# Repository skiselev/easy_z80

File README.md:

# Easy Z80
An easy to build Zilog Z80 based single board computer

## Table of Contents
* [Introduction](#introduction)
* [Specifications](#specifications)
* [Hardware Documentation](#hardware-documentation)
  * [Schematic and PCB Layout](#schematic-and-pcb-layout)
  * [Connectors and Jumpers](#connectors-and-jumpers)
  * [Bill of Materials](#bill-of-materials)
* [Firmware Documentation](#firmware-documentation)
  * [BIOS and OS](#bios-and-os)
  * [SPLD Fuse Map](#spld-fuse-map)
* [Release Notes](#release-notes)
  * [Changes](#changes)
  * [Known Issues](#known-issues)
  * [Wishlist](#wishlist)

## Introduction
My son Max asked me what it takes to build a computer, and whether or not he can design and build one himself. This project is our attempt to design and build a simple, easy to understand, yet capable single board computer.
It reuses the same memory paging mechanism I've implemented in Zeta SBC V2. It uses the Zilog Z80 SIO/O, Z80 CTC peripheral ICs, and implements daisy chain mode 2 interrupt configuration.

## Specifications
* Processor: Zilog Z80 CPU (CMOS version - Z84C00)
* Memory: 512 KiB battery-backed SRAM, 512 KiB Flash ROM
* I/O:
  * Zilog Z80 CTC - Programmable timer used for periodic interrupts and (optionally) for generating UART clock
  * Zilog Z80 SIO - Dual channel serial interface, used for console and for connecting to other peripheral devices
* Bus: [RC2014](https://rc2014.co.uk/) compatible
* Microprocessor Supervisor:
  * Reset generation
  * SRAM battery backup
  * Power failure NMI
  * Watchdog (optional)

## Hardware Documentation

For the version 1.0 schematic, PCB layout, and bill of materials please refer to [tag v1.0](https://github.com/skiselev/easy_z80/tree/v1.0)

### Schematic and PCB Layout

[Schematic - Version 1.1](KiCad/Easy_Z80-Schematic-1.1.pdf)

[PCB Layout - Version 1.1](KiCad/Easy_Z80-Board-1.1.pdf)

### Connectors and Jumpers

#### J1 - Power
Connect regulated +5V power supply to this connector.

Pin                     | Signal Name | Description
----------------------- | ----------- | -----------
Tip (the inner contact)	| VCC         | Positive terminal - +5V
Barrel / sleeve	        | GND         | Negative terminal - ground

#### J2, J3 - Serial Channel A and Serial Channel B
Pin    | Signal Name | Description
------ | ----------- | -----------
1	     | DCD         |	Carrier Detect; Not used - Not connected on the SBC
2	     | RXA, RXB    |	Receive Data; Input to SBC
3	     | TXA, TXB    |	Transmit Data; Output from SBC
4	     | DTR         |	Data Terminal Ready; Not used - Not connected on the SBC
5	     | GND         |	Connected to the SBC GND signal
6	     | DSR         | Data Set Ready; Not used - Not connected on the SBC
7      |	RTSA, RTSB  | Request to Send; Output from SBC
8	     | CTSA, CTSB  | Clear to Send; Input to SBC
9	     | RI	         | Ring Indicator; Not used - Not connected on the SBC
Shield	| DE9 Shield	 | Connected to the SBC GND signal

#### J4 - NVRAM Battery
Connect 3V battery for SRAM backup to this connector.

**Important: If the SRAM battery backup is not desired, short J4 with a jumper. Do not leave this connector open.**

Pin | Signal Name | Description
--- | ----------- | -----------
1  	| VBAT        | Positive terminal - +3V
2   | GND         | Negative terminal - ground

#### J5, J6, J7 - RC2014 Bus
Pin   | Signal Name | Description         | Pin  | Signal Name | Description
----- | ----------- | ------------------- | ---- | ----------- | -----------
J5-1  | A15         | Address A15; Output |      |             |
J5-2  | A14         | Address A14; Output |      |             |
J5-3  | A13         | Address A13; Output |      |             |
J5-4  | A12         | Address A12; Output |      |             |
J5-5  | A11         | Address A11; Output |      |             |
J5-6  | A10         | Address A10; Output |      |             |
J5-7  | A9          | Address A9; Output  |      |             |
J5-8  | A8          | Address A8; Output  |      |             |
J5-9  | A7          | Address A7; Output  |      |             |
J5-10 | A6          | Address A6; Output  |      |             |
J5-11 | A5          | Address A5; Output  |      |             |
J5-12 | A4          | Address A4; Output  |      |             |
J5-13 | A3          | Address A3; Output  |      |             |
J5-14 | A2          | Address A2; Output  |      |             |
J5-15 | A1          | Address A1; Output  |      |             |
J5-16 | A0          | Address A0; Output  |      |             |
J5-17 | GND         | Ground              | J6-1 | GND         | Ground
J5-18 | VCC         | Power Supply - +5V  | J6-2 | VCC         | Power Supply - +5V
J5-19 | /M1         | Machine Cycle One; Output | J6-3| /RFSH | DRAM refresh; Output
J5-20 | /RESET      | Reset; Output       | J6-4 | N/C         | Not connected
J5-21 | CPU_CLK     | CPU Clock; Output   | J6-5 | UART_CLK    | UART Clock (1.8432 MHz); Output
J5-22 | /INT        | Interrupt; Input    | J6-6 | /BUSACK     | DMA Bus Acknowledge; Output
J5-23 | /MREQ       | Memory Request; Output | J6-7 | /HALT    | Halt; Output
J5-24 | /WR         | Write Request; Output | J6-8 | /BUSREQ   | DMA Bus Request; Input
J5-25 | /RD         | Read Request; Output | J6-9 | /WAIT      | Wait; Input
J5-26 | /IORQ       | Input/Output Request; Output | J6-10 | /NMI | Non-maskable Interrupt; Input
J5-27 | D0          | Data D0; Input/Output |    |             |
J5-28 | D1          | Data D1; Input/Output |    |             |
J5-29 | D2          | Data D2; Input/Output |    |             |
J5-30 | D3          | Data D3; Input/Output |    |             |
J5-31 | D4          | Data D4; Input/Output |    |             |
J5-32 | D5          | Data D5; Input/Output |    |             |
J5-33 | D6          | Data D6; Input/Output |    |             |
J5-34 | D7          | Data D7; Input/Output |    |             |
J5-35 | TXDA        | Channel A, Transmit Data; Output | J7-1 | TXDB | Channel B, Transmit Data; Output
J5-36 | RXDA        | Channel A, Receive Data; Input   | J7-2 | RXDB | Channel B, Receive Data; Input
J5-37 | USR1        | User Pin 1, Not connected | J7-3 | USR5  | User Pin 5, Not connected 
J5-38 | IEI         | Interrupt Enable Input  | J7-4 | USR6    | User Pin 6, Not connected 
J5-39 | IEO         | Interrupt Enable Output | J7-5 | USR7    | User Pin 7, Not connected 

#### JP1 - Serial Channel A Clock Select
Position        | Description
--------------- | -----------
*1-2 (default)* | 1.8432 MHz (115200 bps if using x16 mode)
2-3             | Programmable using CTC channel 0

#### JP2 - Serial Channel B Clock Select
Position        | Description
--------------- | -----------
*1-2 (default)* | 1.8432 MHz (115200 bps if using x16 mode)
2-3             | Programmable using CTC channel 1

### Bill of Materials

#### Version 1.1

[Easy Z80 project on Mouser.com](https://www.mouser.com/ProjectManager/ProjectDetail.aspx?AccessID=f16751cb33) - View and order all components except of the PCB.

[Easy Z80 project on OSH Park](https://oshpark.com/shared_projects/Rt7SBcRg) - View and order the PCB.

Component type     | Reference | Description                                 | Quantity | Possible sources and notes 
------------------ | --------- | ------------------------------------------- | -------- | --------------------------
PCB                |           | Easy Z80 PCB - Version 1.1                  | 1        | Refer to the [RetroBrew Computers Board Inventory](https://www.retrobrewcomputers.org/doku.php?id=boardinventory#minimal_8085_z80_single_board_computer) page for ordering information, or order from a PCB manufacturer of your choice using provided Gerber or KiCad files
Integrated Circuit | U1        | Z80 CPU, CMOS, 40 pin DIP - Z84C00xxPEG     | 1        | Mouser [692-Z84C0010PEG](https://www.mouser.com/ProductDetail/692-Z84C0010PEG)
Integrated Circuit | U2        | Z80 CTC, CMOS, 28 pin DIP - Z84C30xxPEG     | 1        | Mouser [692-Z84C3010PEG](https://www.mouser.com/ProductDetail/692-Z84C3010PEG)
Integrated Circuit | U3        | Z80 SIO/0, CMOS, 40 pin DIP - Z84C40xxPEG   | 1        | Mouser [692-Z84C4010PEG](https://www.mouser.com/ProductDetail/692-Z84C4010PEG)
Integrated Circuit | U4        | 512 KiB SRAM, 32 pin DIP - AS6C4008         | 1        | Mouser [913-AS6C4008-55PCN](https://www.mouser.com/ProductDetail/913-AS6C4008-55PCN)
Integrated Circuit | U5        | 512 KiB Flash ROM, 32 pin DIP - SST39SF040  | 1        | Mouser [804-39SF0407CPHE](https://www.mouser.com/ProductDetail/804-39SF0407CPHE)
Integrated Circuit | U6        | Microprocessor Supervisory Circuit - MAX693 | 1        | Mouser [584-ADM693ANZ](https://www.mouser.com/ProductDetail/584-ADM693ANZ); Possible alternatives: MAX693, LTC693, ADM691, MAX691, LTC691, ADM695, MAX695, LTC965, LTC1235
Integrated Circuit | U7, U8    | Dual RS-232 Driver/Receiver - MAX232A       | 2        | Mouser [595-TRS202EIN](https://www.mouser.com/ProductDetail/595-TRS202EIN/)
Integrated Circuit | U9        | Simple Programmable Logic Device - ATF16V8B | 1        | Mouser [556-AF16V8B15PU](https://www.mouser.com/ProductDetail/556-AF16V8B15PU)
Integrated Circuit | U10, U11  | 4-by-4 Register File - 74HC670              | 2        | Mouser [595-CD74HC670E](https://www.mouser.com/ProductDetail/595-CD74HC670E)
Integrated Circuit | U12       | Dual Flip Flop - 74HC74                     | 1        | Mouser [595-SN74HC74N](https://www.mouser.com/ProductDetail/595-SN74HC74N)
Oscillator         | QG1       | 10 MHz, CMOS oscillator, Half Can           | 1        | Mouser [774-MXO45HS-3C-10.0](https://www.mouser.com/ProductDetail/774-MXO45HS-3C-10.0)
Oscillator         | QG2       | 1.8432 MHz, CMOS oscillator, Half Can       | 1        | Mouser [774-MXO45HS-3C-1.8](https://www.mouser.com/ProductDetail/774-MXO45HS-3C-1.8)
LED                | D1        | 3 mm, green LED indicator                   | 1        | Mouser [859-LTL-4231N](https://www.mouser.com/ProductDetail/859-LTL-4231N)
Tactile Button     | SW1       | 6 mm tactile button, right angle            | 1        | Mouser [653-B3F-3152](https://www.mouser.com/ProductDetail/653-B3F-3152)
Connector          | J1        | DC Power Jack, 2mm                          | 1        | Mouser [806-KLDX-0202-A](https://www.mouser.com/ProductDetail/806-KLDX-0202-A)
Connector          | J2, J3    | Sub-D DE9M, Right Angle, PCB mount          | 2        | Mouser [806-K22X-E9P-N-99](https://www.mouser.com/ProductDetail/806-K22X-E9P-N-99)
Connector          | J4        | 2 Pin Header with Friction Lock             | 1        | Mouser [571-6404562](https://www.mouser.com/ProductDetail/571-6404562)
Pin Header         | J5 - J7   | 40x2 Pin Header, 2.54 mm Pitch, Right Angle | 1        | Mouser [571-9-103326-0](https://www.mouser.com/ProductDetail/571-9-103326-0)
Capacitor          | C1 - C14, C16 - C23  | 0.1 uF, MLCC, 5 mm Pitch         | 22       | Mouser [594-K104K15X7RF53H5](https://www.mouser.com/ProductDetail/594-K104K15X7RF53H5)
Capacitor          | C24       | 47 uF, 25V, Aluminum Organic Polymer        | 1        | Mouser [80-A750EK476M1EAAE40](https://www.mouser.com/ProductDetail/80-A750EK476M1EAAE40)
Resistor Array     | RN1 - RN3 | 4.7 k, bussed, 5 pin SIP                    | 3        | Mouser [652-4605X-AP1-472LF](https://www.mouser.com/ProductDetail/652-4605X-AP1-472LF)
Resistor Array     | RN4       | 4.7 k, bussed, 9 pin SIP                    | 1        | Mouser [652-4609X-AP1-472LF](https://www.mouser.com/ProductDetail/652-4609X-AP1-472LF)
Resistor           | R1        | 470 ohm, axial                              | 1        | Mouser [603-MFR-25FRF52-470R](https://www.mouser.com/ProductDetail/603-MFR-25FRF52-470R) 
Resistor           | R2 - R4   | 10 kohm, 1% tolerance, axial                | 3        | Mouser [603-MFR-25FRF5210K](https://www.mouser.com/ProductDetail/603-MFR-25FRF5210K)
Resistor           | R5        | 29.4 kohm, 1% tolerance, axial              | 1        | Mouser [603-MFR-25FBF52-29K4](https://www.mouser.com/ProductDetail/603-MFR-25FBF52-29K4)
Trimmer Resistor   | RV1       | 2 kohm, through hole                        | 1        | Mouser [652-3362P-1-202LF](https://www.mouser.com/ProductDetail/652-3362P-1-202LF)
IC Socket          | U1, U3    | 40 pin DIP                                  | 2        | Mouser [517-4840-6000-CP](https://www.mouser.com/ProductDetail/517-4840-6000-CP)
IC Socket          | U4, U5    | 32 pin DIP                                  | 2        | Mouser [517-4832-6000-CP](https://www.mouser.com/ProductDetail/517-4832-6000-CP)
IC Socket          | U2        | 28 pin DIP                                  | 1        | Mouser [517-4828-6000-CP](https://www.mouser.com/ProductDetail/517-4828-6000-CP)
IC Socket          | U9        | 20 pin DIP                                  | 1        | Mouser [517-4820-3000-CP](https://www.mouser.com/ProductDetail/517-4820-3000-CP)
IC Socket          | U6 - U8, U10, U11 | 16 pin DIP                          | 5        | Mouser [517-4816-3000-CP](https://www.mouser.com/ProductDetail/517-4816-3000-CP)
IC Socket          | U12       | 14 pin DIP                                  | 1        | Mouser [517-4814-3000-CP](https://www.mouser.com/ProductDetail/517-4814-3000-CP)
Oscillator Socket  | QG1, QG2  | 4 pin DIP, Half Can                         | 2        | Mouser [535-1108800](https://www.mouser.com/ProductDetail/535-1108800)

## Firmware Documentation

### BIOS and OS

Easy Z80 is supported by [RomWBW](https://github.com/wwarthen/RomWBW) [v2.9.1](https://github.com/wwarthen/RomWBW/releases/tag/v2.9.1) and later. RomWBW includes BIOS, CP/M-80 2.2, Z-System, and a collection of utilities. It also should be possible to run [FUZIX](https://github.com/EtchedPixels/FUZIX) on this board.

### SPLD Fuse Map

Easy Z80 uses an ATF16V8/GAL16V8 SPLD (U9) for address decode logic. The [SPLD fuse map](SPLD/easy_z80_no_wdog.jed) and the [SPLD source code](SPLD/easy_z80_no_wdog.pld) are provided in [SPLD](SPLD) directory of this repository.

## Release Notes

### Changes
* Version 1.1
  * Add pull-up resistors on the data bus (RN4 - 4.7k) to support Z80 interrupt mode 0
  * Use 74HC series instead of 74HCT
  * Remove C15
  * Use RN reference for resistor arrays instead of RR
  * Update silkscreen:
    * Make RN1 reference and value visible
    * Update silkscreen of headers footprints, so that JP1 and JP2 don't cover the traces
    * Add project URL to the bottom silkscreen
* Version 1.0
  * Initial version

### Known Issues
* Version 1.0
  * Top silkscreen: RR1 reference and value are not visible. It should read "RR1, 4.7k"
  * Bottom silkscreen on JP1 and JP2 covers the trace connections, so they are not easily visible
  * Bottom silkscreen: No project URL. Should be [github.com/skiselev/easy_z80](https://github.com/skiselev/easy_z80)
  * Board will not reset when C15 is populated. Workaround: Do not populate this capacitor
  * Schematic and top silkscreen: Use 74HC series instead of 74HCT
  
### Wishlist
* Version 1.0
  * Add pull-ups on the data bus to support extension boards that were not designed for Z80 interrupt mode 2

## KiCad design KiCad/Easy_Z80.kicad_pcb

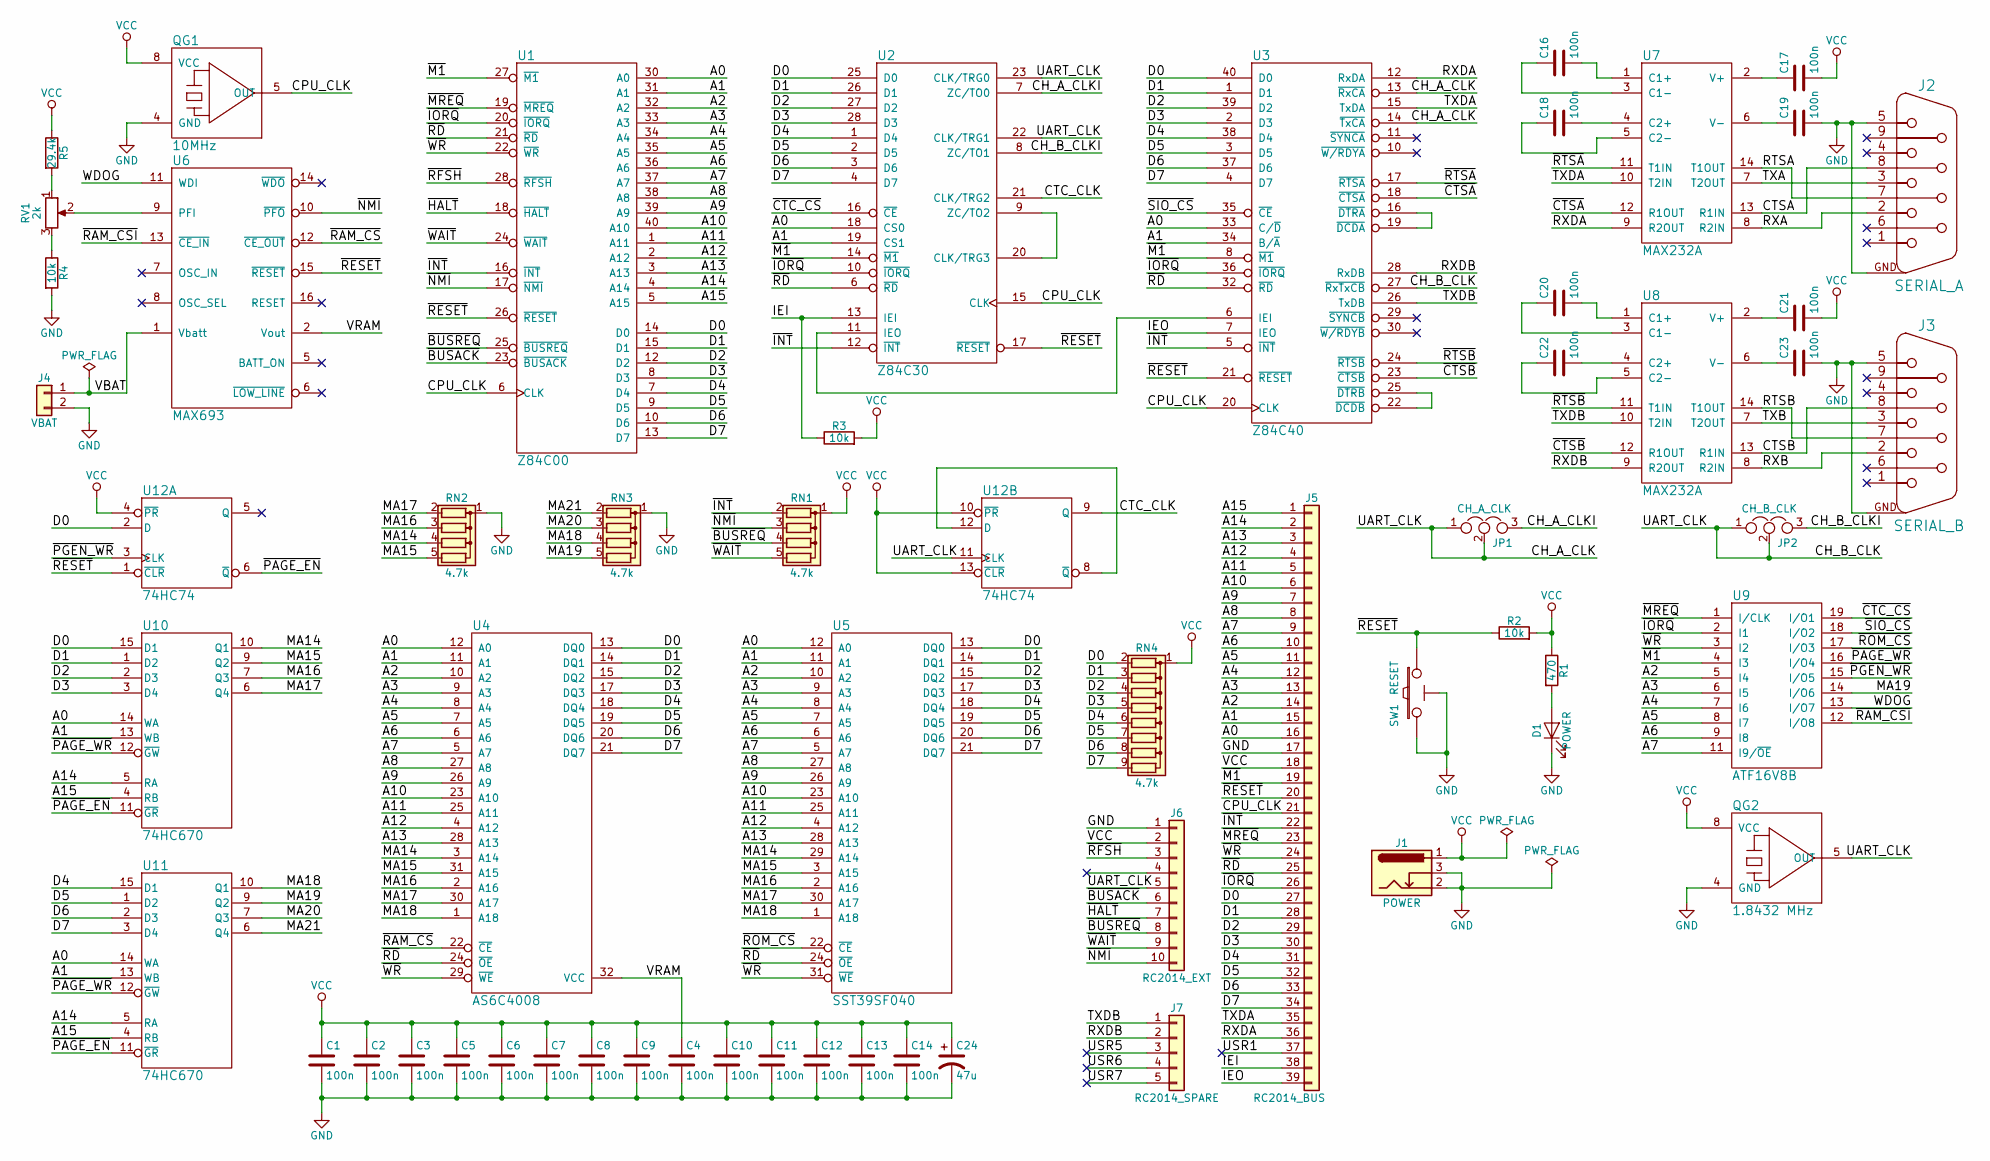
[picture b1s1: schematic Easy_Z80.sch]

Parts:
C1, C2, C3, C4, C5, C6, C7, C8, C9, C10, C11, C12, C13, C14, C16, C17, C18, C19, C20, C21, C22, C23: 100n; Cap_Cer_508
C24: 47u; Cap_Elec_Radial_6.3mm
D1: POWER; LED_3mm
J1: POWER; Conn_Power_Jack_Circular_Pads
J2: SERIAL_A; Conn_Dsub_DE9M
J3: SERIAL_B; Conn_Dsub_DE9M
J4: VBAT; Conn_Friction_Lock_2P_2.54mm
J5: RC2014_BUS; Conn_Pin_Header_39x1_2.54mm
J6: RC2014_EXT; Conn_Pin_Header_10x1_2.54mm
J7: RC2014_SPARE; Conn_Pin_Header_5x1_2.54mm
JP1: CH_A_CLK; Conn_Pin_Header_3x1_2.54mm
JP2: CH_B_CLK; Conn_Pin_Header_3x1_2.54mm
QG1: 10MHz; OSC_Half_Can_DIP8
QG2: 1.8432 MHz; OSC_Half_Can_DIP8
R1: 470; Res_762
R2, R3, R4: 10k; Res_762
R5: 29.4k; Res_762
RN1, RN2, RN3: 4.7k; Conn_SIL5
RN4: 4.7k; Conn_SIL9
RV1: 2k; Trimmer_Bourns_3362P
SW1: RESET; Switch_Tactile_6mm_Right
U1: Z84C00; IC_DIP40_600
U2: Z84C30; IC_DIP28_600
U3: Z84C40; IC_DIP40_600
U4: AS6C4008; IC_DIP32_600
U5: SST39SF040; IC_DIP32_600
U6: MAX693; IC_DIP16_300
U7, U8: MAX232A; IC_DIP16_300
U9: ATF16V8B; IC_DIP20_300
U10, U11: 74HC670; IC_DIP16_300
U12: 74HC74; IC_DIP14_300

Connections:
/A0: J5.16, U1.30 (A0), U2.18 (CS0), U3.33 (C/~D), U4.12 (A0), U5.12 (A0), U10.14 (WA), U11.14 (WA)
/A1: J5.15, U1.31 (A1), U2.19 (CS1), U3.34 (B/~A), U4.11 (A1), U5.11 (A1), U10.13 (WB), U11.13 (WB)
/A2: J5.14, U1.32 (A2), U4.10 (A2), U5.10 (A2), U9.5 (I4)
/A3: J5.13, U1.33 (A3), U4.9 (A3), U5.9 (A3), U9.6 (I5)
/A4: J5.12, U1.34 (A4), U4.8 (A4), U5.8 (A4), U9.7 (I6)
/A5: J5.11, U1.35 (A5), U4.7 (A5), U5.7 (A5), U9.8 (I7)
/A6: J5.10, U1.36 (A6), U4.6 (A6), U5.6 (A6), U9.9 (I8)
/A7: J5.9, U1.37 (A7), U4.5 (A7), U5.5 (A7), U9.11 (I9/~OE)
/A8: J5.8, U1.38 (A8), U4.27 (A8), U5.27 (A8)
/A9: J5.7, U1.39 (A9), U4.26 (A9), U5.26 (A9)
/A10: J5.6, U1.40 (A10), U4.23 (A10), U5.23 (A10)
/A11: J5.5, U1.1 (A11), U4.25 (A11), U5.25 (A11)
/A12: J5.4, U1.2 (A12), U4.4 (A12), U5.4 (A12)
/A13: J5.3, U1.3 (A13), U4.28 (A13), U5.28 (A13)
/A14: J5.2, U1.4 (A14), U10.5 (RA), U11.5 (RA)
/A15: J5.1, U1.5 (A15), U10.4 (RB), U11.4 (RB)
/CH_A_CLK: J6.5, JP1.1, JP1.2, JP2.1, JP2.2, QG2.5 (OUT), U2.22 (CLK/TRG1), U2.23 (CLK/TRG0), U3.13 (~RxCA), U3.14 (~TxCA), U3.27 (~RxTxCB), U12.11 (CLK)
/CH_A_CLKI: JP1.3, U2.7 (ZC/TO0)
/CH_B_CLKI: JP2.3, U2.8 (ZC/TO1)
/CPU_CLK: J5.21, QG1.5 (OUT), U1.6 (CLK), U2.15 (CLK), U3.20 (CLK)
/CTC_CLK: U2.21 (CLK/TRG2), U12.9 (Q)
/CTSA: J2.8, U7.13 (R1IN)
/CTSB: J3.8, U8.13 (R1IN)
/D0: J5.27, RN4.2 (R1), U1.14 (D0), U2.25 (D0), U3.40 (D0), U4.13 (DQ0), U5.13 (DQ0), U10.15 (D1), U12.2 (D)
/D1: J5.28, RN4.3 (R2), U1.15 (D1), U2.26 (D1), U3.1 (D1), U4.14 (DQ1), U5.14 (DQ1), U10.1 (D2)
/D2: J5.29, RN4.4 (R3), U1.12 (D2), U2.27 (D2), U3.39 (D2), U4.15 (DQ2), U5.15 (DQ2), U10.2 (D3)
/D3: J5.30, RN4.5 (R4), U1.8 (D3), U2.28 (D3), U3.2 (D3), U4.17 (DQ3), U5.17 (DQ3), U10.3 (D4)
/D4: J5.31, RN4.6 (R5), U1.7 (D4), U2.1 (D4), U3.38 (D4), U4.18 (DQ4), U5.18 (DQ4), U11.15 (D1)
/D5: J5.32, RN4.7 (R6), U1.9 (D5), U2.2 (D5), U3.3 (D5), U4.19 (DQ5), U5.19 (DQ5), U11.1 (D2)
/D6: J5.33, RN4.8 (R7), U1.10 (D6), U2.3 (D6), U3.37 (D6), U4.20 (DQ6), U5.20 (DQ6), U11.2 (D3)
/D7: J5.34, RN4.9 (R8), U1.13 (D7), U2.4 (D7), U3.4 (D7), U4.21 (DQ7), U5.21 (DQ7), U11.3 (D4)
/IEI: J5.38, R3.1, U2.13 (IEI)
/IEO: J5.39, U3.7 (IEO)
/MA14: RN2.4 (R3), U4.3 (A14), U5.29 (A14), U10.10 (Q1)
/MA15: RN2.5 (R4), U4.31 (A15), U5.3 (A15), U10.9 (Q2)
/MA16: RN2.3 (R2), U4.2 (A16), U5.2 (A16), U10.7 (Q3)
/MA17: RN2.2 (R1), U4.30 (A17), U5.30 (A17), U10.6 (Q4)
/MA18: RN3.4 (R3), U4.1 (A18), U5.1 (A18), U11.10 (Q1)
/MA19: RN3.5 (R4), U9.14 (I/O6), U11.9 (Q2)
/MA20: RN3.3 (R2), U11.7 (Q3)
/MA21: RN3.2 (R1), U11.6 (Q4)
/RTSA: J2.7, U7.14 (T1OUT)
/RTSB: J3.7, U8.14 (T1OUT)
/RXA: J2.2, U7.8 (R2IN)
/RXB: J3.2, U8.8 (R2IN)
/RXDA: J5.36, U3.12 (RxDA), U7.9 (R2OUT)
/RXDB: J7.2, U3.28 (RxDB), U8.9 (R2OUT)
/TXA: J2.3, U7.7 (T2OUT)
/TXB: J3.3, U8.7 (T2OUT)
/TXDA: J5.35, U3.15 (TxDA), U7.10 (T2IN)
/TXDB: J7.1, U3.26 (TxDB), U8.10 (T2IN)
/USR1: J5.37
/USR5: J7.3
/USR6: J7.4
/USR7: J7.5
/VBAT: J4.1, U6.1 (Vbatt)
/VRAM: C4.1, U4.32 (VCC), U6.2 (Vout)
/WDOG: U6.11 (WDI), U9.13 (I/O7)
/~BUSACK: J6.6, U1.23 (~BUSACK)
/~BUSREQ: J6.8, RN1.4 (R3), U1.25 (~BUSREQ)
/~CTC_CS: U2.16 (~CE), U9.19 (I/O1)
/~CTSA: U3.18 (~CTSA), U7.12 (R1OUT)
/~CTSB: U3.23 (~CTSB), U8.12 (R1OUT)
/~HALT: J6.7, U1.18 (~HALT)
/~INT: J5.22, RN1.2 (R1), U1.16 (~INT), U2.12 (~INT), U3.5 (~INT)
/~IORQ: J5.26, U1.20 (~IORQ), U2.10 (~IORQ), U3.36 (~IORQ), U9.2 (I1)
/~M1: J5.19, U1.27 (~M1), U2.14 (~M1), U3.8 (~M1), U9.4 (I3)
/~MREQ: J5.23, U1.19 (~MREQ), U9.1 (I/CLK)
/~NMI: J6.10, RN1.3 (R2), U1.17 (~NMI), U6.10 (~PFO)
/~PAGE_EN: U10.11 (~GR), U11.11 (~GR), U12.6 (~Q)
/~PAGE_WR: U9.16 (I/O4), U10.12 (~GW), U11.12 (~GW)
/~PGEN_WR: U9.15 (I/O5), U12.3 (CLK)
/~RAM_CS: U4.22 (~CE), U6.12 (~CE_OUT)
/~RAM_CSI: U6.13 (~CE_IN), U9.12 (I/O8)
/~RD: J5.25, U1.21 (~RD), U2.6 (~RD), U3.32 (~RD), U4.24 (~OE), U5.24 (~OE)
/~RESET: J5.20, R2.1, SW1.1, U1.26 (~RESET), U2.17 (~RESET), U3.21 (~RESET), U6.15 (~RESET), U12.1 (~CLR)
/~RFSH: J6.3, U1.28 (~RFSH)
/~ROM_CS: U5.22 (~CE), U9.17 (I/O3)
/~RTSA: U3.17 (~RTSA), U7.11 (T1IN)
/~RTSB: U3.24 (~RTSB), U8.11 (T1IN)
/~SIO_CS: U3.35 (~CE), U9.18 (I/O2)
/~WAIT: J6.9, RN1.5 (R4), U1.24 (~WAIT)
/~WR: J5.24, U1.22 (~WR), U4.29 (~WE), U5.31 (~WE), U9.3 (I2)
GND: C1.2, C2.2, C3.2, C4.2, C5.2, C6.2, C7.2, C8.2, C9.2, C10.2, C11.2, C12.2, C13.2, C14.2, C19.2, C23.2, C24.2, D1.1 (K), J1.2, J1.3, J2.5, J2.GND, J3.5, J3.GND, J4.2, J5.17, J6.1, QG1.4 (GND), QG2.4 (GND), R4.2, RN2.1 (common), RN3.1 (common), SW1.2, SW1.GND, U1.29 (GND), U2.5 (GND), U3.31 (GND), U4.16 (GND), U5.16 (GND), U6.4 (GND), U7.15 (GND), U8.15 (GND), U9.10 (GND), U10.8 (GND), U11.8 (GND), U12.7 (GND)
unnamed: C16.1, U7.3 (C1-)
unnamed: C16.2, U7.1 (C1+)
unnamed: C17.1, U7.2 (V+)
unnamed: C18.1, U7.5 (C2-)
unnamed: C18.2, U7.4 (C2+)
unnamed: C19.1, U7.6 (V-)
unnamed: C20.1, U8.3 (C1-)
unnamed: C20.2, U8.1 (C1+)
unnamed: C21.1, U8.2 (V+)
unnamed: C22.1, U8.5 (C2-)
unnamed: C22.2, U8.4 (C2+)
unnamed: C23.1, U8.6 (V-)
unnamed: D1.2 (A), R1.2
unnamed: R4.1, RV1.3
unnamed: R5.2, RV1.1
unnamed: RV1.2, U6.9 (PFI)
unnamed: U2.11 (IEO), U3.6 (IEI)
unnamed: U2.9 (ZC/TO2), U2.20 (CLK/TRG3)
unnamed: U3.16 (~DTRA), U3.19 (~DCDA)
unnamed: U3.22 (~DCDB), U3.25 (~DTRB)
unnamed: U12.8 (~Q), U12.12 (D)
VCC: C1.1, C2.1, C3.1, C5.1, C6.1, C7.1, C8.1, C9.1, C10.1, C11.1, C12.1, C13.1, C14.1, C17.2, C21.2, C24.1, J1.1, J5.18, J6.2, QG1.8 (VCC), QG2.8 (VCC), R1.1, R2.2, R3.2, R5.1, RN1.1 (common), RN4.1 (common), U1.11 (VCC), U2.24 (VCC), U3.9 (VCC), U5.32 (VCC), U6.3 (VCC), U7.16 (VCC), U8.16 (VCC), U9.20 (VCC), U10.16 (VCC), U11.16 (VCC), U12.4 (~PR), U12.10 (~PR), U12.13 (~CLR), U12.14 (VCC)

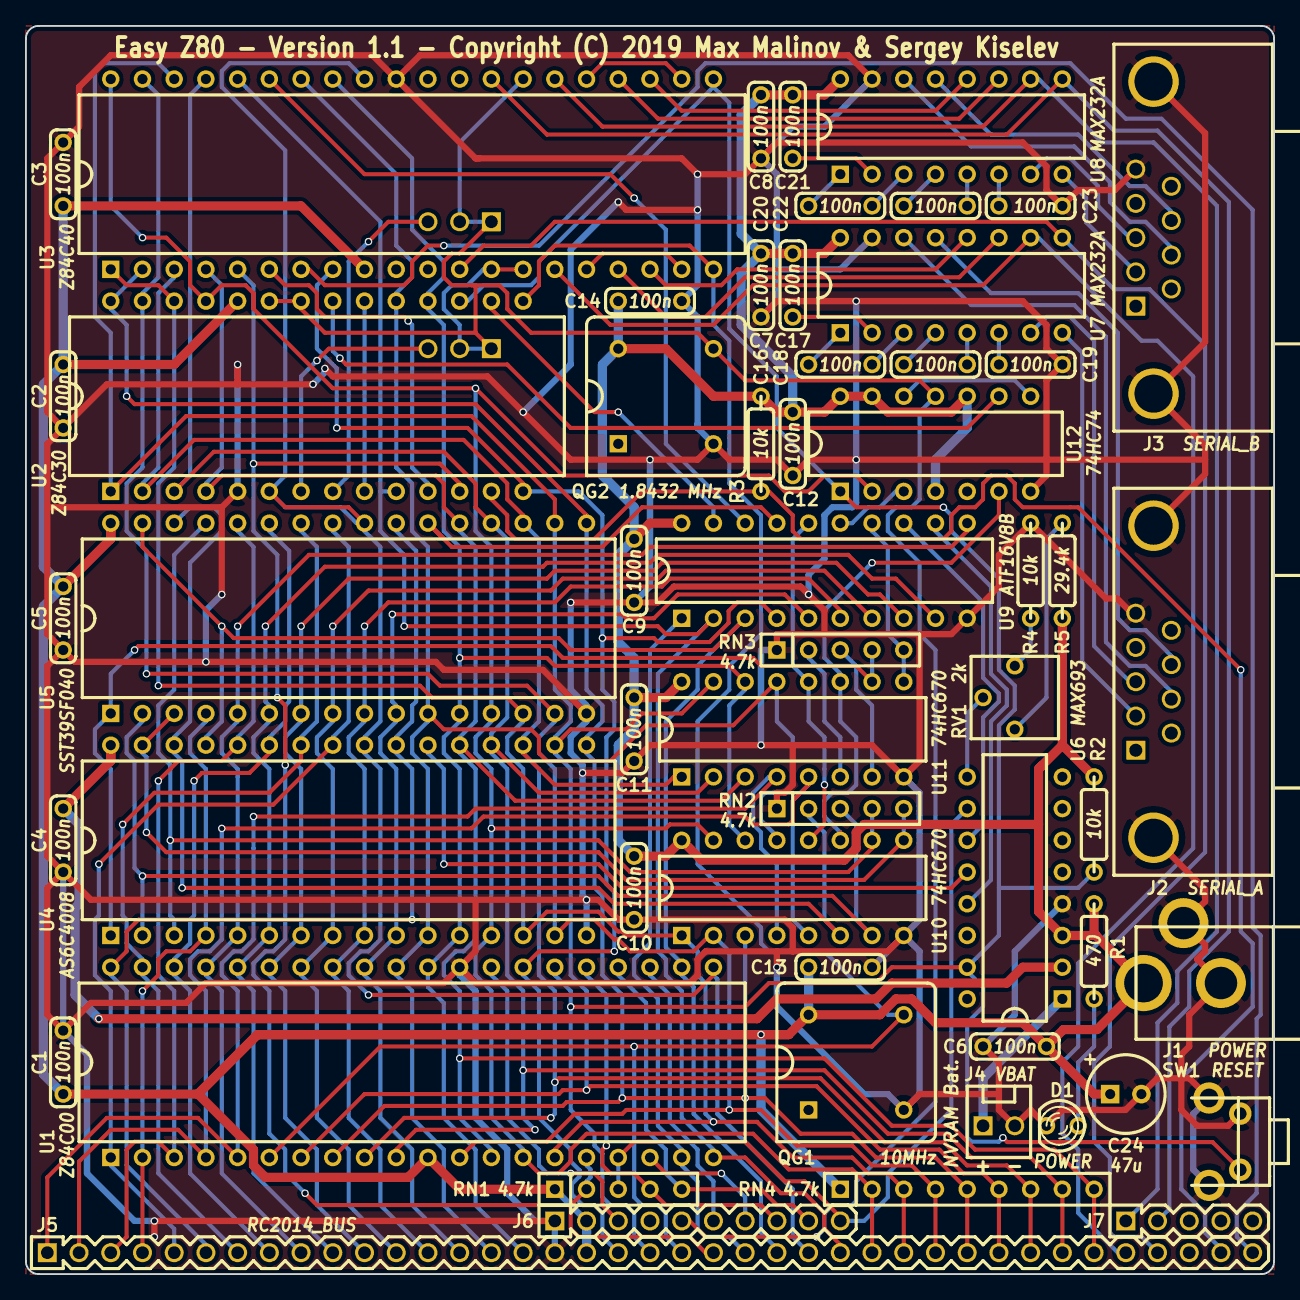
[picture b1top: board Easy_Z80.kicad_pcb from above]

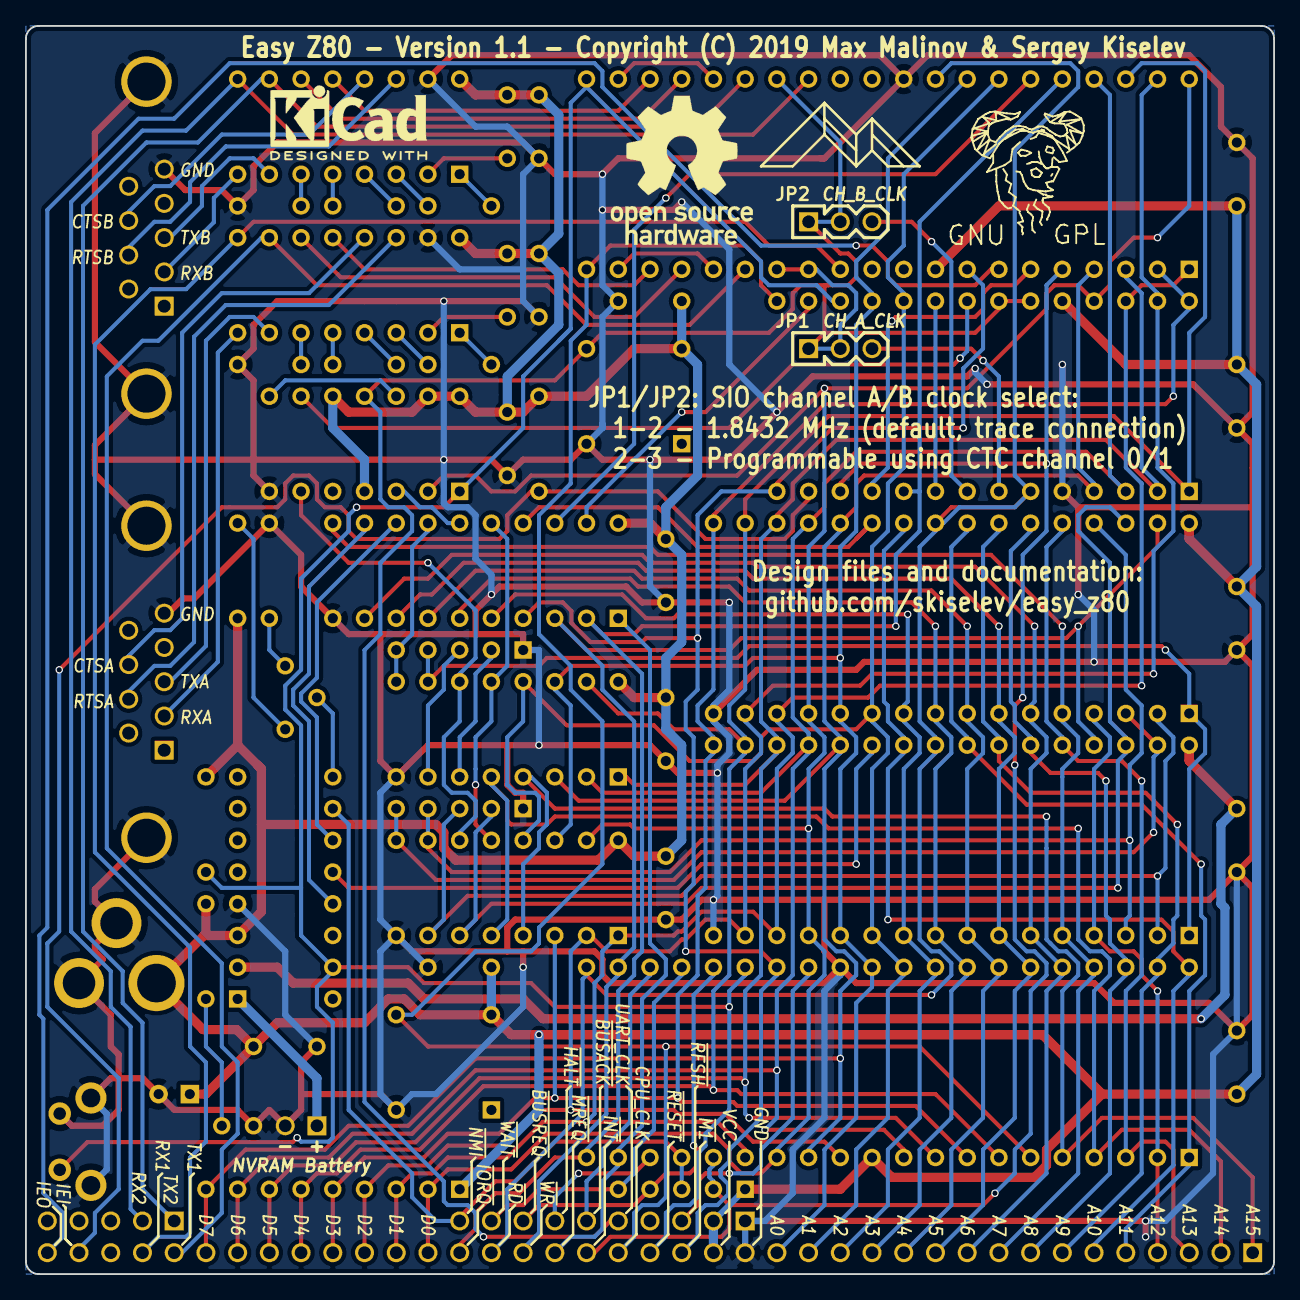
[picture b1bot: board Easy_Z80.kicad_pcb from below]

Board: 2 copper layers, 99.9 x 99.9 mm, 58 parts (2 on the bottom side), 102 nets.

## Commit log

2019-02-07 README: BOM: Fix quantities; use 1% resistors
    Fix the quantity of 470 ohm resistors, 10 kohm resistors, and 14 pin DIP sockets
    Use 1% resistors to reduce the number of different parts
2019-02-07 README: Add connectors documentation
2019-02-07 README: Add jumpers description
2019-02-07 README: Add PCB rendering, schematic and board layout links
2019-02-07 Add KiCad, Gerber and Documentation
2019-02-07 Add resized PCB rendering
2019-02-07 Update resized PCB rendering
2019-02-07 README: Add firmware documentation
2019-02-07 Add SPLD fuse maps
2019-02-15 Add Known Issues for 1.0
2019-02-15 PCB: Silkscreen fixes
2019-02-26 SPLD: Add fusemap without watchdog
2019-02-27 SPLD: fix pin mapping
2019-02-27 README: Replace PCB rendering with the board photo; Describe C15 reset issue.
2019-02-27 Add a photo of the assembled board
2019-02-27 Update the photo of the assembled board
2019-03-01 Add microprocessor supervisor info
2019-03-05 README: Clarify peripherals and interrupt mode
2019-03-07 README: Add data bus pull-ups to the wishlist
2019-03-07 SPLD: Move watchdog to 0x6C-0x6F to avoid conflict with RC2014 secondary SIO board
2019-03-07 SPLD: Update fusemaps with the previous PLD change
2019-03-07 SPLD: Update JED with the previous PLD change
2019-03-08 README: Add table of content
2019-03-08 SPLD: Move CTC to 0x88-0x8B
2019-03-11 README: Add alternatives for ADM693
2019-04-05 README: Use 74HC instead of 74HCT
2019-06-12 KiCad: Replace files with version 1.1
2019-06-12 Gerber: Replace files with version 1.1
2019-06-12 README: Update design files links. Add changes for version 1.1
2019-06-12 README: BOM and Changes updates for version 1.1
2019-06-12 README: Update link to the Oshpark project for version 1.1
2019-06-12 README: Add RomWBW v2.9.1 to firmware section
2019-06-12 README: Update BOM version 1.1
2019-06-13 README: BOM - PCB version is 1.1
2019-07-23 README: Add a note on the J4 connector
2020-06-30 README.md: fix U3 # of pins and link to JEDEC file
    The SIO is a 40 pin DIP. There are two JEDEC files, w/ and w/o watchdog.
    Link to the one w/o watchdog support.
2021-01-29 README: Fix a typo (BUSREQ signal missing) in the RC2014 bus description
2021-02-19 README: Replace TRS232 with TRS202E
2021-02-19 README: Replace 603-MFR-25FBF52-470R with 603-MFR-25FRF52-470R (same part, but available at Mouser)
2026-01-21 Fix typos in README.md

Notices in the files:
KiCad/Easy_Z80.kicad_pcb:
Easy Z80 - Version 1.1 - Copyright (C) 2019 Max Malinov & Sergey Kiselev
